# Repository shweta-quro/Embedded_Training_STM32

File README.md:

# Embedded_Training_STM32
STM32 Training Repo

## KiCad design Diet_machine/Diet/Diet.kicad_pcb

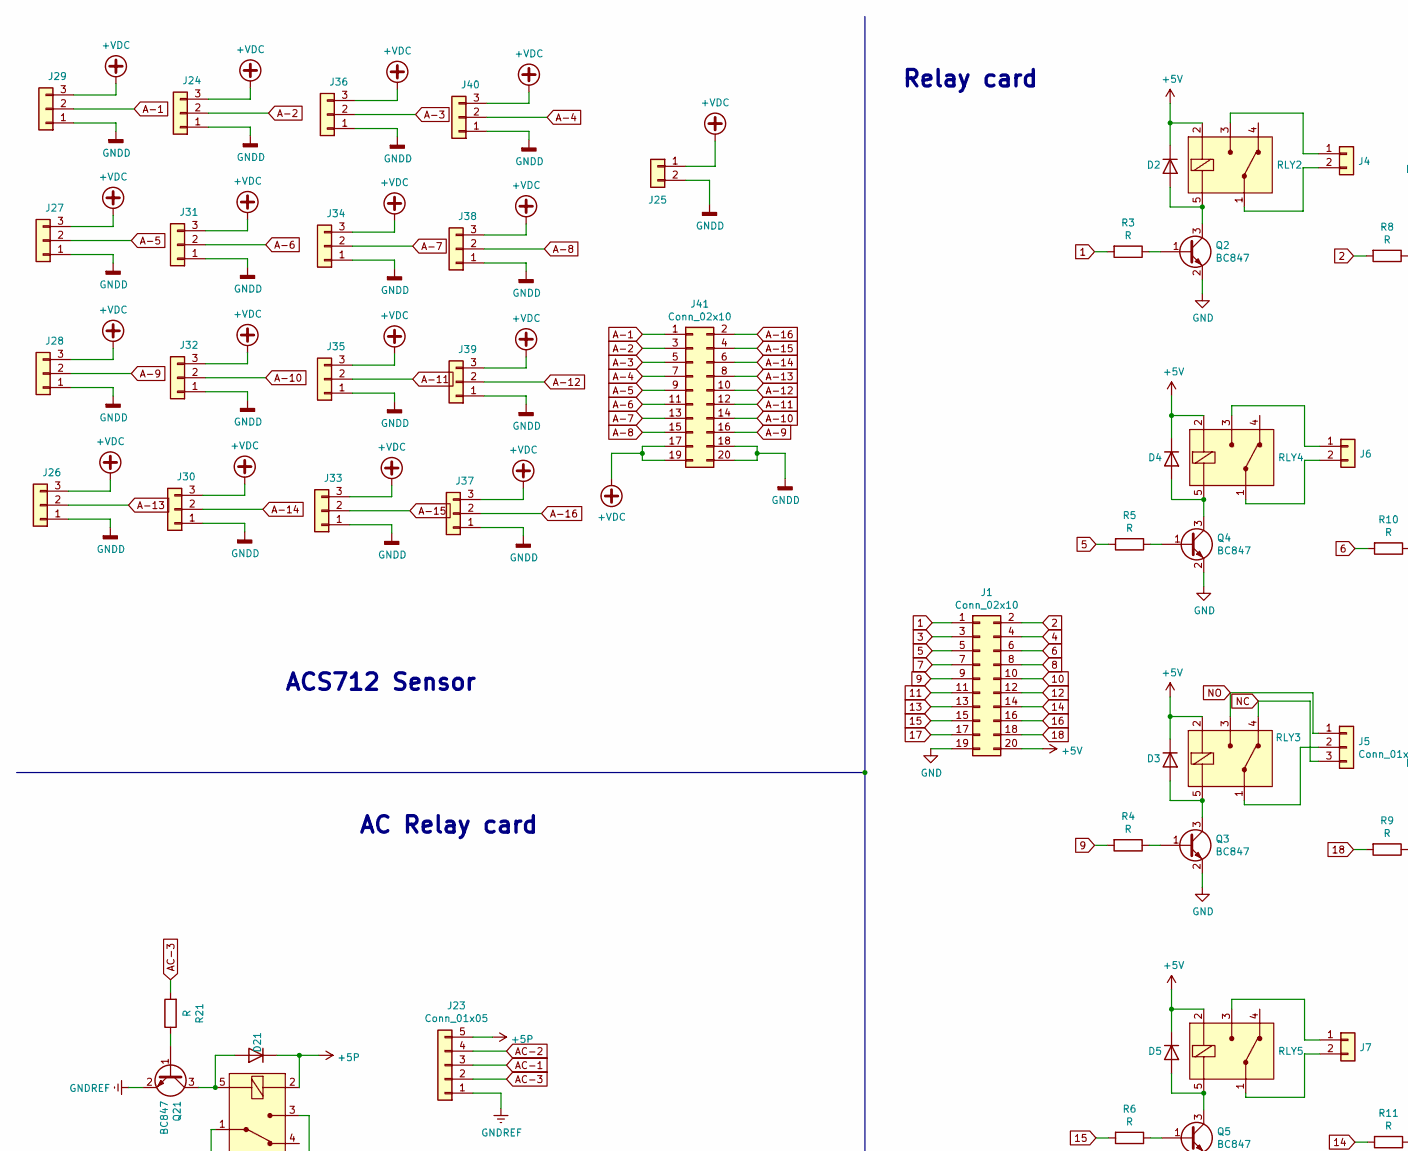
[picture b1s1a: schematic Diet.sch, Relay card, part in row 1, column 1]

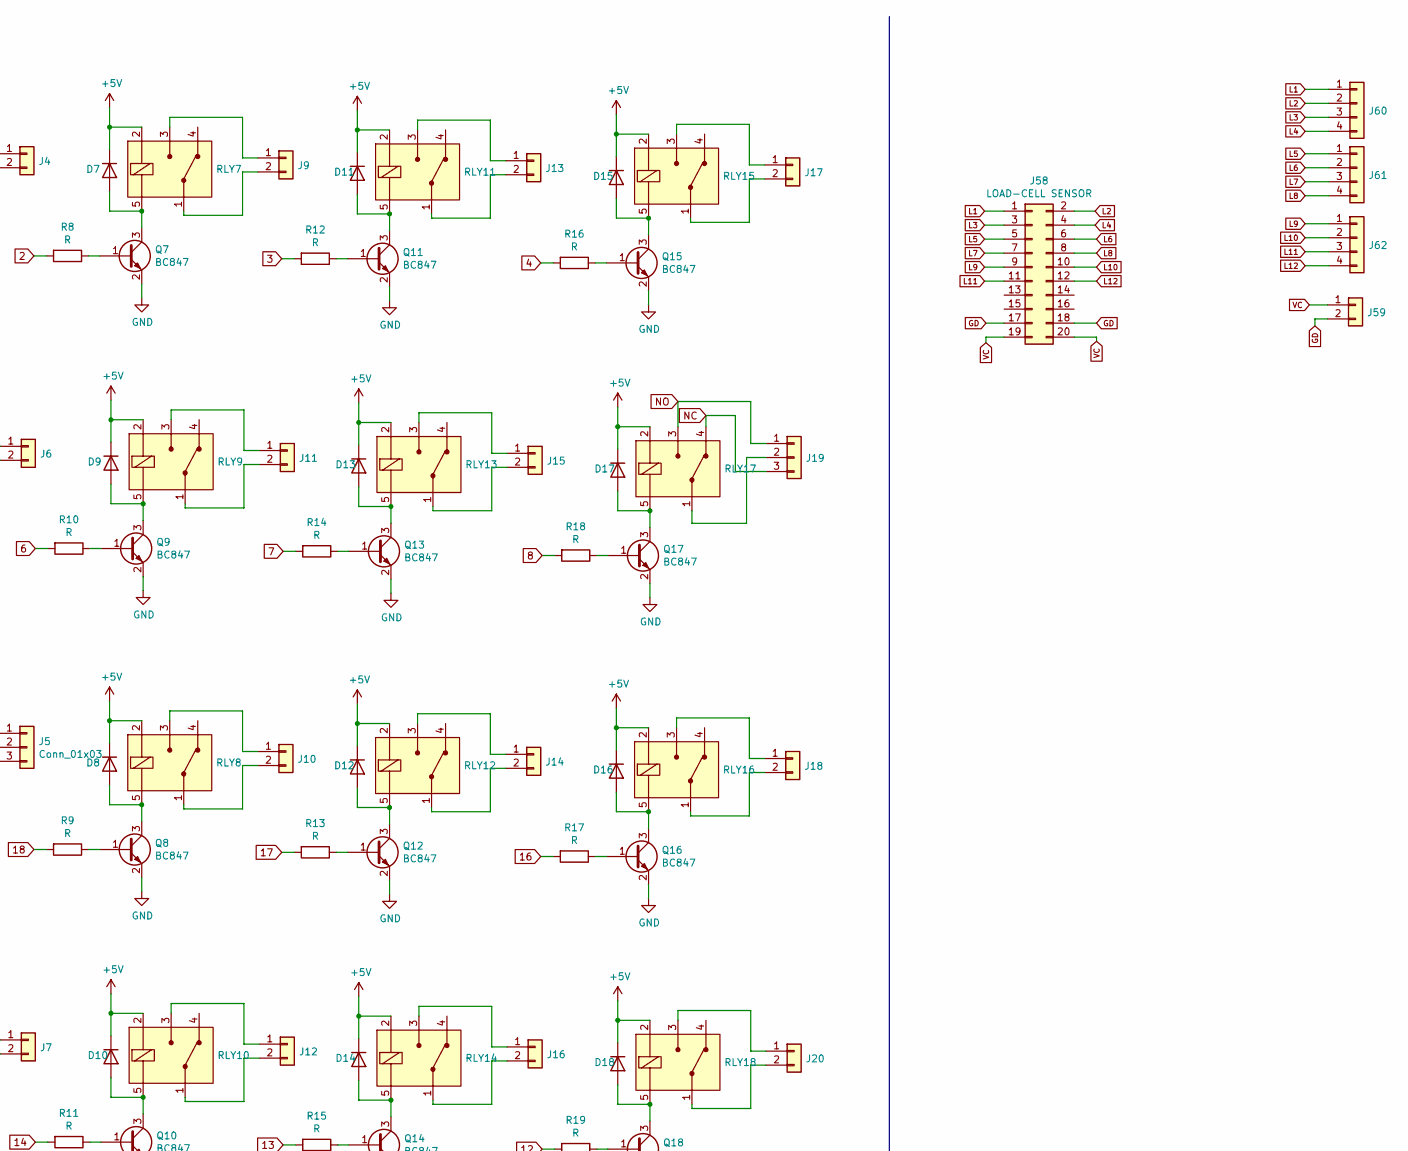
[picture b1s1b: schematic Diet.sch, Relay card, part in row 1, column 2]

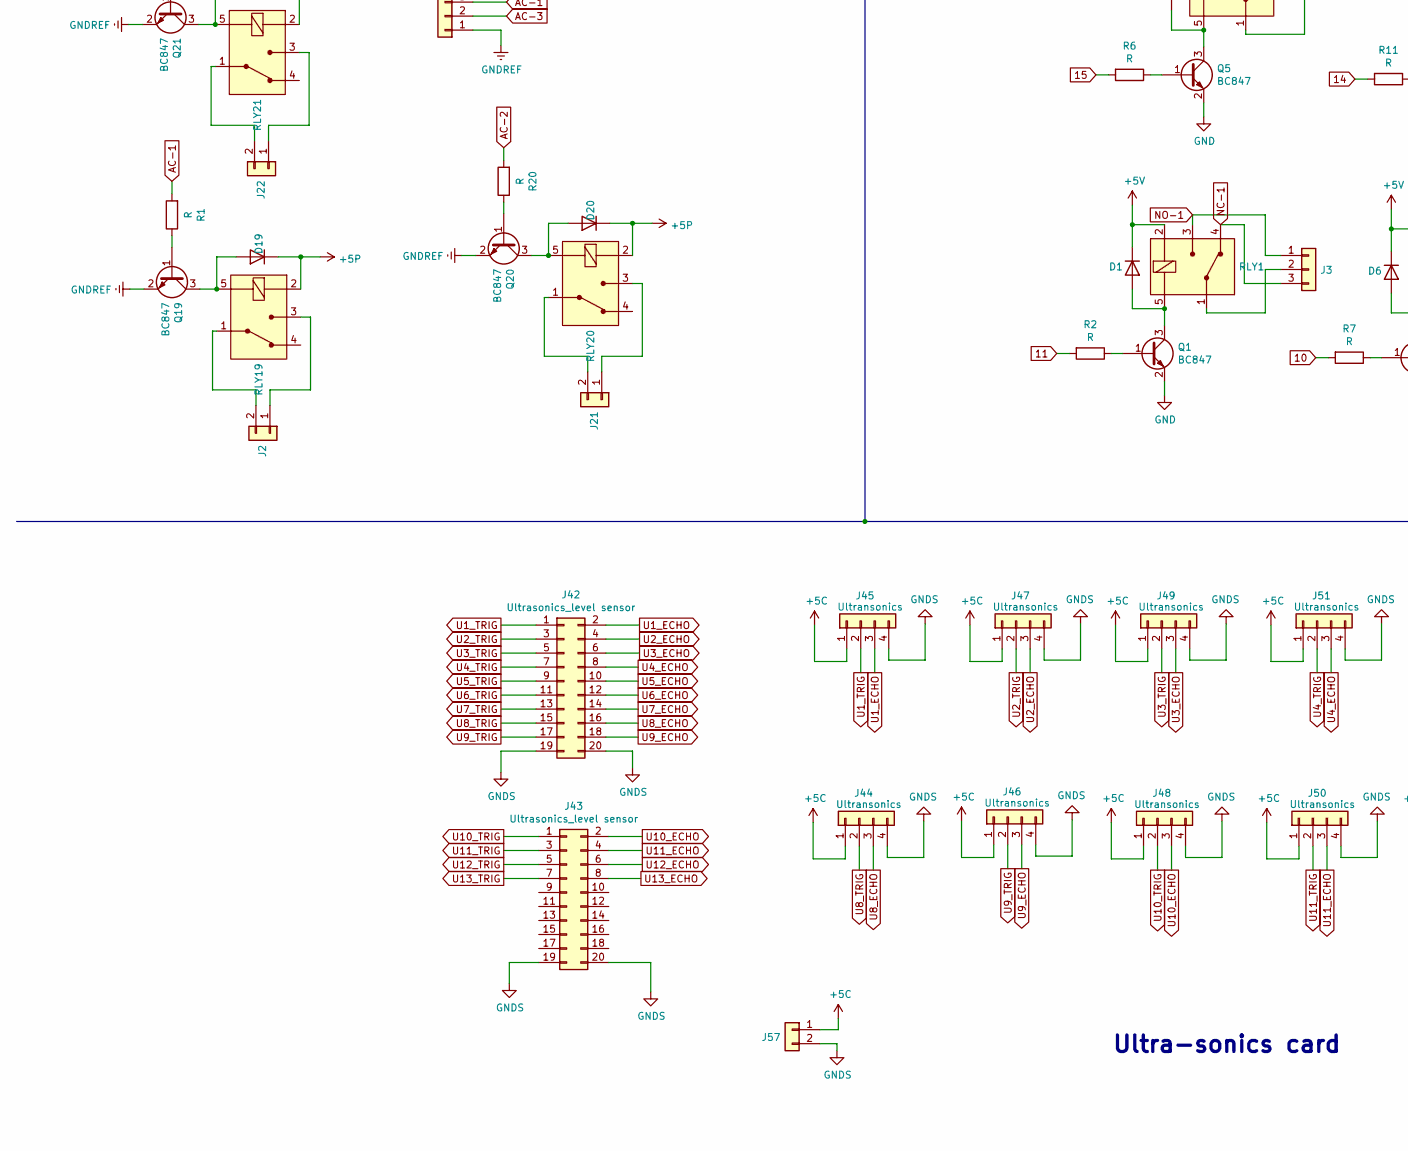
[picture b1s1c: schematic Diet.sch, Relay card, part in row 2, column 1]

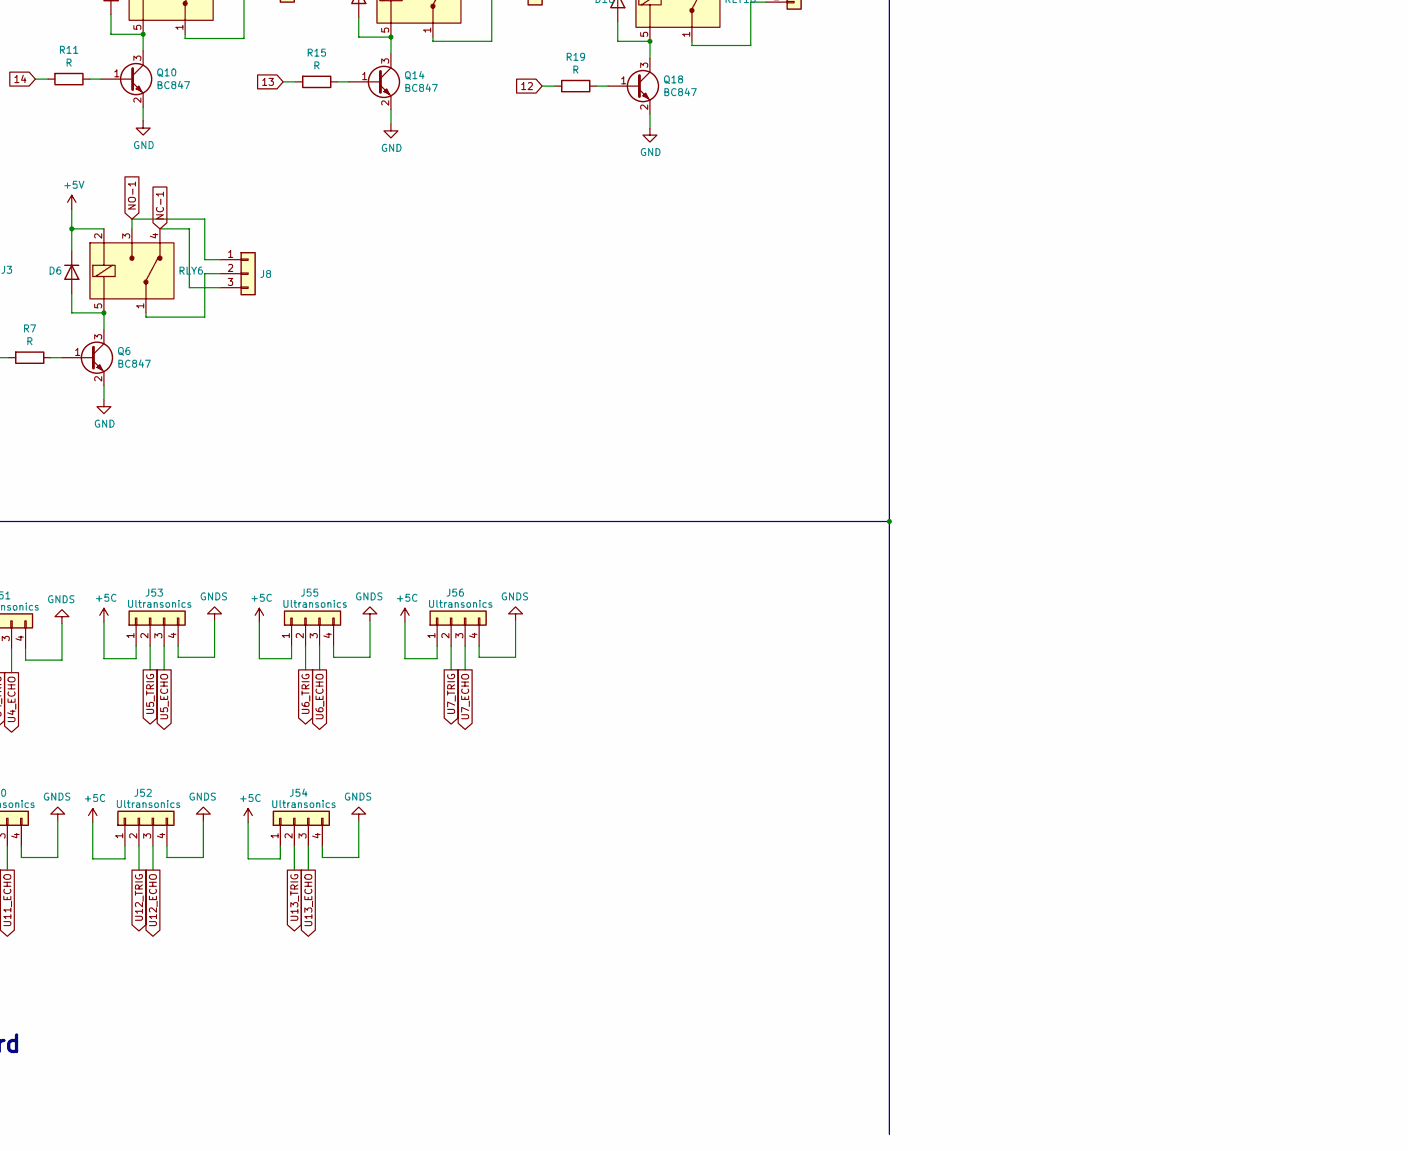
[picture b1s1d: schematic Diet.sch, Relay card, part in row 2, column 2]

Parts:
D1, D2, D3, D4, D5, D6, D7, D8, D9, D10, D11, D12, D13, D14, D15, D16, D17, D18, D19, D20, D21: SM4007; D_MELF
J1, J41: Conn_02x10; IDC-Header_2x10_P2.54mm_Vertical
J2, J4, J6, J7, J9, J10, J11, J12, J13, J14, J15, J16, J17, J18, J20, J21, J22, J25, J57, J59: 5.08mm; PhoenixContact_MCV_1,5_2-G-5.08_1x02_P5.08mm_Vertical
J3, J5, J8, J19: Conn_01x03; PhoenixContact_MCV_1,5_3-G-5.08_1x03_P5.08mm_Vertical
J23: Conn_01x05; PhoenixContact_MCV_1,5_5-G-5.08_1x05_P5.08mm_Vertical
J24, J26, J27, J28, J29, J30, J31, J32, J33, J34, J35, J36, J37, J38, J39, J40: Conn_01x03; PinHeader_1x03_P2.54mm_Vertical
J42, J43: Ultrasonics_level sensor; IDC-Header_2x10_P2.54mm_Vertical
J44, J45, J46, J47, J48, J49, J50, J51, J52, J53, J54, J55, J56: Ultransonics; Molex_KK-254_AE-6410-04A_1x04_P2.54mm_Vertical
J58: LOAD-CELL SENSOR; IDC-Header_2x10_P2.54mm_Vertical
J60, J61, J62: Conn_01x04; PhoenixContact_MCV_1,5_4-G-5.08_1x04_P5.08mm_Vertical
Q1, Q2, Q3, Q4, Q5, Q6, Q7, Q8, Q9, Q10, Q11, Q12, Q13, Q14, Q15, Q16, Q17, Q18, Q19, Q20, Q21: BC847; SOT-23
R1, R2, R3, R4, R5, R6, R7, R8, R9, R10, R11, R12, R13, R14, R15, R16, R17, R18, R19, R20, R21: R; R_0805_2012Metric_Pad1.20x1.40mm_HandSolder
RLY1, RLY2, RLY3, RLY4, RLY5, RLY6, RLY7, RLY8, RLY9, RLY10, RLY11, RLY12, RLY13, RLY14, RLY15, RLY16, RLY17, RLY18, RLY19, RLY20, RLY21: G5LE-14_DC5-dk_Power-Relays-Over-2-Amps; Relay_THT_G5LE-14; MPN G5LE-14 DC5; Digi-Key_PN Z1011-ND

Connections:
1: J1.1, R3.2
2: J1.2, R8.2
3: J1.3, R12.2
4: J1.4, R16.2
5: J1.5, R5.2
6: J1.6, R10.2
7: J1.7, R14.2
8: J1.8, R18.2
9: J1.9, R4.2
10: J1.10, R7.2
11: J1.11, R2.2
12: J1.12, R19.2
13: J1.13, R15.2
14: J1.14, R11.2
15: J1.15, R6.2
16: J1.16, R17.2
17: J1.17, R13.2
18: J1.18, R9.2
+5C: J44.1, J45.1, J46.1, J47.1, J48.1, J49.1, J50.1, J51.1, J52.1, J53.1, J54.1, J55.1, J56.1, J57.1
+5P: D19.1 (K), D20.1 (K), D21.1 (K), J23.5, RLY19.2 (COIL), RLY20.2 (COIL), RLY21.2 (COIL)
+5V: D1.1 (K), D2.1 (K), D3.1 (K), D4.1 (K), D5.1 (K), D6.1 (K), D7.1 (K), D8.1 (K), D9.1 (K), D10.1 (K), D11.1 (K), D12.1 (K), D13.1 (K), D14.1 (K), D15.1 (K), D16.1 (K), D17.1 (K), D18.1 (K), J1.20, RLY1.2 (COIL), RLY2.2 (COIL), RLY3.2 (COIL), RLY4.2 (COIL), RLY5.2 (COIL), RLY6.2 (COIL), RLY7.2 (COIL), RLY8.2 (COIL), RLY9.2 (COIL), RLY10.2 (COIL), RLY11.2 (COIL), RLY12.2 (COIL), RLY13.2 (COIL), RLY14.2 (COIL), RLY15.2 (COIL), RLY16.2 (COIL), RLY17.2 (COIL), RLY18.2 (COIL)
+VDC: J24.3, J25.1, J26.3, J27.3, J28.3, J29.3, J30.3, J31.3, J32.3, J33.3, J34.3, J35.3, J36.3, J37.3, J38.3, J39.3, J40.3, J41.17, J41.19
A-1: J29.2, J41.1
A-2: J24.2, J41.3
A-3: J36.2, J41.5
A-4: J40.2, J41.7
A-5: J27.2, J41.9
A-6: J31.2, J41.11
A-7: J34.2, J41.13
A-8: J38.2, J41.15
A-9: J28.2, J41.16
A-10: J32.2, J41.14
A-11: J35.2, J41.12
A-12: J39.2, J41.10
A-13: J26.2, J41.8
A-14: J30.2, J41.6
A-15: J33.2, J41.4
A-16: J37.2, J41.2
AC-1: J23.3, R1.2
AC-2: J23.4, R20.2
AC-3: J23.2, R21.2
GD: J58.17, J58.18, J59.2
GND: J1.19, Q1.2 (E), Q2.2 (E), Q3.2 (E), Q4.2 (E), Q5.2 (E), Q6.2 (E), Q7.2 (E), Q8.2 (E), Q9.2 (E), Q10.2 (E), Q11.2 (E), Q12.2 (E), Q13.2 (E), Q14.2 (E), Q15.2 (E), Q16.2 (E), Q17.2 (E), Q18.2 (E)
GNDD: J24.1, J25.2, J26.1, J27.1, J28.1, J29.1, J30.1, J31.1, J32.1, J33.1, J34.1, J35.1, J36.1, J37.1, J38.1, J39.1, J40.1, J41.18, J41.20
GNDREF: J23.1, Q19.2 (E), Q20.2 (E), Q21.2 (E)
GNDS: J42.19, J42.20, J43.19, J43.20, J44.4, J45.4, J46.4, J47.4, J48.4, J49.4, J50.4, J51.4, J52.4, J53.4, J54.4, J55.4, J56.4, J57.2
L1: J58.1, J60.1
L2: J58.2, J60.2
L3: J58.3, J60.3
L4: J58.4, J60.4
L5: J58.5, J61.1
L6: J58.6, J61.2
L7: J58.7, J61.3
L8: J58.8, J61.4
L9: J58.9, J62.1
L10: J58.10, J62.2
L11: J58.11, J62.3
L12: J58.12, J62.4
NC: J5.3, J19.3, RLY3.4 (NC), RLY17.4 (NC)
NC-1: J3.3, J8.3, RLY1.4 (NC), RLY6.4 (NC)
NO: J5.1, J19.1, RLY3.3 (NO), RLY17.3 (NO)
NO-1: J3.1, J8.1, RLY1.3 (NO), RLY6.3 (NO)
unnamed: D1.2 (A), Q1.3 (C), RLY1.5 (COIL)
unnamed: D2.2 (A), Q2.3 (C), RLY2.5 (COIL)
unnamed: D3.2 (A), Q3.3 (C), RLY3.5 (COIL)
unnamed: D4.2 (A), Q4.3 (C), RLY4.5 (COIL)
unnamed: D5.2 (A), Q5.3 (C), RLY5.5 (COIL)
unnamed: D6.2 (A), Q6.3 (C), RLY6.5 (COIL)
unnamed: D7.2 (A), Q7.3 (C), RLY7.5 (COIL)
unnamed: D8.2 (A), Q8.3 (C), RLY8.5 (COIL)
unnamed: D9.2 (A), Q9.3 (C), RLY9.5 (COIL)
unnamed: D10.2 (A), Q10.3 (C), RLY10.5 (COIL)
unnamed: D11.2 (A), Q11.3 (C), RLY11.5 (COIL)
unnamed: D12.2 (A), Q12.3 (C), RLY12.5 (COIL)
unnamed: D13.2 (A), Q13.3 (C), RLY13.5 (COIL)
unnamed: D14.2 (A), Q14.3 (C), RLY14.5 (COIL)
unnamed: D15.2 (A), Q15.3 (C), RLY15.5 (COIL)
unnamed: D16.2 (A), Q16.3 (C), RLY16.5 (COIL)
unnamed: D17.2 (A), Q17.3 (C), RLY17.5 (COIL)
unnamed: D18.2 (A), Q18.3 (C), RLY18.5 (COIL)
unnamed: D19.2 (A), Q19.3 (C), RLY19.5 (COIL)
unnamed: D20.2 (A), Q20.3 (C), RLY20.5 (COIL)
unnamed: D21.2 (A), Q21.3 (C), RLY21.5 (COIL)
unnamed: J2.1, RLY19.3 (NO)
unnamed: J2.2, RLY19.1 (COM)
unnamed: J3.2, RLY1.1 (COM)
unnamed: J4.1, RLY2.3 (NO)
unnamed: J4.2, RLY2.1 (COM)
unnamed: J5.2, RLY3.1 (COM)
unnamed: J6.1, RLY4.3 (NO)
unnamed: J6.2, RLY4.1 (COM)
unnamed: J7.1, RLY5.3 (NO)
unnamed: J7.2, RLY5.1 (COM)
unnamed: J8.2, RLY6.1 (COM)
unnamed: J9.1, RLY7.3 (NO)
unnamed: J9.2, RLY7.1 (COM)
unnamed: J10.1, RLY8.3 (NO)
unnamed: J10.2, RLY8.1 (COM)
unnamed: J11.1, RLY9.3 (NO)
unnamed: J11.2, RLY9.1 (COM)
unnamed: J12.1, RLY10.3 (NO)
unnamed: J12.2, RLY10.1 (COM)
unnamed: J13.1, RLY11.3 (NO)
unnamed: J13.2, RLY11.1 (COM)
unnamed: J14.1, RLY12.3 (NO)
unnamed: J14.2, RLY12.1 (COM)
unnamed: J15.1, RLY13.3 (NO)
unnamed: J15.2, RLY13.1 (COM)
unnamed: J16.1, RLY14.3 (NO)
unnamed: J16.2, RLY14.1 (COM)
unnamed: J17.1, RLY15.3 (NO)
unnamed: J17.2, RLY15.1 (COM)
unnamed: J18.1, RLY16.3 (NO)
unnamed: J18.2, RLY16.1 (COM)
unnamed: J19.2, RLY17.1 (COM)
unnamed: J20.1, RLY18.3 (NO)
unnamed: J20.2, RLY18.1 (COM)
unnamed: J21.1, RLY20.3 (NO)
unnamed: J21.2, RLY20.1 (COM)
unnamed: J22.1, RLY21.3 (NO)
unnamed: J22.2, RLY21.1 (COM)
unnamed: Q1.1 (B), R2.1
unnamed: Q2.1 (B), R3.1
unnamed: Q3.1 (B), R4.1
unnamed: Q4.1 (B), R5.1
unnamed: Q5.1 (B), R6.1
unnamed: Q6.1 (B), R7.1
unnamed: Q7.1 (B), R8.1
unnamed: Q8.1 (B), R9.1
unnamed: Q9.1 (B), R10.1
unnamed: Q10.1 (B), R11.1
unnamed: Q11.1 (B), R12.1
unnamed: Q12.1 (B), R13.1
unnamed: Q13.1 (B), R14.1
unnamed: Q14.1 (B), R15.1
unnamed: Q15.1 (B), R16.1
unnamed: Q16.1 (B), R17.1
unnamed: Q17.1 (B), R18.1
unnamed: Q18.1 (B), R19.1
unnamed: Q19.1 (B), R1.1
unnamed: Q20.1 (B), R20.1
unnamed: Q21.1 (B), R21.1
U1_ECHO: J42.2, J45.3
U1_TRIG: J42.1, J45.2
U2_ECHO: J42.4, J47.3
U2_TRIG: J42.3, J47.2
U3_ECHO: J42.6, J49.3
U3_TRIG: J42.5, J49.2
U4_ECHO: J42.8, J51.3
U4_TRIG: J42.7, J51.2
U5_ECHO: J42.10, J53.3
U5_TRIG: J42.9, J53.2
U6_ECHO: J42.12, J55.3
U6_TRIG: J42.11, J55.2
U7_ECHO: J42.14, J56.3
U7_TRIG: J42.13, J56.2
U8_ECHO: J42.16, J44.3
U8_TRIG: J42.15, J44.2
U9_ECHO: J42.18, J46.3
U9_TRIG: J42.17, J46.2
U10_ECHO: J43.2, J48.3
U10_TRIG: J43.1, J48.2
U11_ECHO: J43.4, J50.3
U11_TRIG: J43.3, J50.2
U12_ECHO: J43.6, J52.3
U12_TRIG: J43.5, J52.2
U13_ECHO: J43.8, J54.3
U13_TRIG: J43.7, J54.2
VC: J58.19, J58.20, J59.1

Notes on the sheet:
ACS712 Sensor
Relay card
AC Relay card
Ultra-sonics card

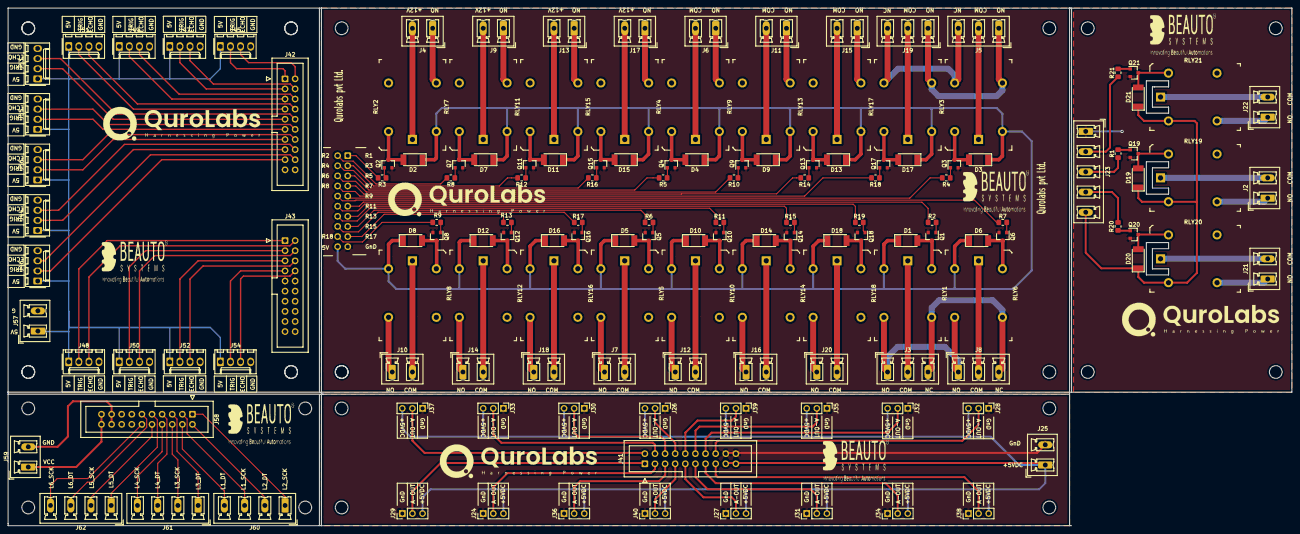
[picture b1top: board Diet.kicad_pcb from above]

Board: 2 copper layers, 322.6 x 130.0 mm, 146 parts (1 on the bottom side), 169 nets.

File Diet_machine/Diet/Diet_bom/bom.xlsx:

Sr.No | Sourced | Placed | References | Value | Footprint | Quantity
1 |  |  | R1, R2, R3, R4, R5, R6, R7, R8, R9, R10, R11, R12, R13, R14, R15, R16, R17, R18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 | R | R_0805_2012Metric_Pad1.20x1.40mm_HandSolder | 21
2 |  |  | D1, D2, D3, D4, D5, D6, D7, D8, D9, D10, D11, D12, D13, D14, D15, D16, D17, D18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 | SM4007 | D_MELF | 21
3 |  |  | Q1, Q2, Q3, Q4, Q5, Q6, Q7, Q8, Q9, Q10, Q11, Q12, Q13, Q14, Q15, Q16, Q17, Q18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 | BC847 | SOT-23 | 21
4 | inhouse |  | RLY1, RLY2, RLY3, RLY4, RLY5, RLY6, RLY7, RLY8, RLY9, RLY10, RLY11, RLY12, RLY1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 | G5LE-14_DC5-dk_Power-Relays-Over-2-Amps | Relay_THT_G5LE-14 | 21
7 |  |  | J2, J4, J6, J7, J9, J10, J11, J12, J13, J14, J15, J16, J17, J18, J20, J21, J22,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 | 5.08mm | PhoenixContact_MCV_1,5_2-G-5.08_1x02_P5.08mm_Vertical | 20
8 |  |  | J24, J26, J27, J28, J29, J30, J31, J32, J33, J34, J35, J36, J37, J38, J39, J40 | Conn_01x03 | PinHeader_1x03_P2.54mm_Vertical | 16
9 |  |  | J44, J45, J46, J47, J48, J49, J50, J51, J52, J53, J54, J55, J56 | Ultransonics | Molex_KK-254_AE-6410-04A_1x04_P2.54mm_Vertical | 13
10 |  |  | J3, J5, J8, J19 | Conn_01x03 | PhoenixContact_MCV_1,5_3-G-5.08_1x03_P5.08mm_Vertical | 4
11 |  |  | J60, J61, J62 | Conn_01x04 | PhoenixContact_MCV_1,5_4-G-5.08_1x04_P5.08mm_Vertical | 3
12 |  |  | J1, J41 | Conn_02x10 | IDC-Header_2x10_P2.54mm_Vertical | 2
13 |  |  | J42, J43 | Ultrasonics_level sensor | IDC-Header_2x10_P2.54mm_Vertical | 2
14 |  |  | J23 | Conn_01x05 | PhoenixContact_MCV_1,5_5-G-5.08_1x05_P5.08mm_Vertical | 1
15 |  |  | J58 | LOAD-CELL SENSOR | IDC-Header_2x10_P2.54mm_Vertical | 1
